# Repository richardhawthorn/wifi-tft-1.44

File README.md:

### Features

- ESP8266 wifi processor
- 128*128 SPI TFT screen
- FTDI chip + FTDI programming port
- 3.3V operation
- Mini USB power connector

### License

This work is licensed under a Creative Commons Attribution-ShareAlike 4.0 International License.

<br />
Designed by <a xmlns:cc="http://creativecommons.org/ns#" href="http://www.richardhawthorn.com" property="cc:attributionName" rel="cc:attributionURL" target="_blank">Richard Hawthorn</a><br />
<a rel="license" href="http://creativecommons.org/licenses/by-sa/4.0/" target="_blank">View License</a>

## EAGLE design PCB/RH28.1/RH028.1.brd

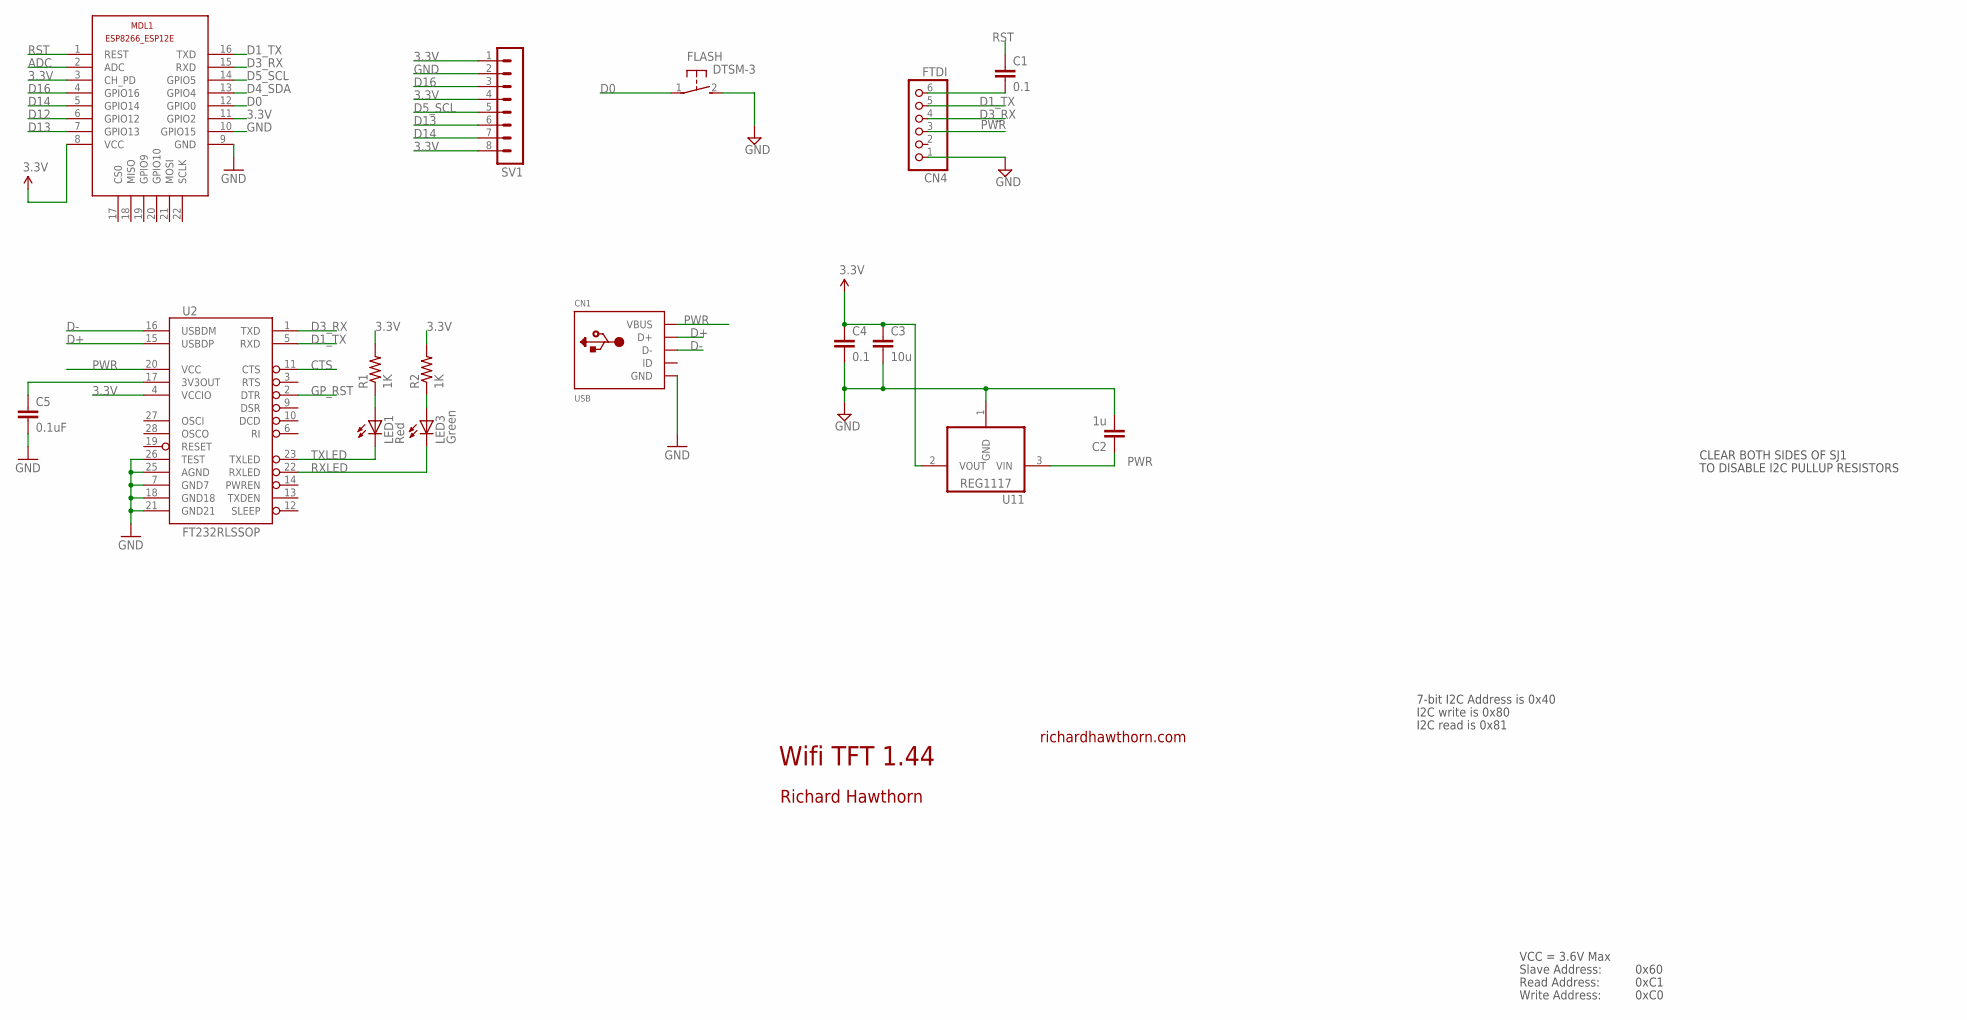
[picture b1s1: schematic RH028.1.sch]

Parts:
C1, C4: 0.1; 0603-CAP
C2: 1u; 0603-CAP
C3: 10u; 0805-CAP
C5: 0.1uF; 0402-CAP
CN1: USB; USB-MINIB
CN4: FTDI; 1X06
FLASH: DTSM-3
LED1: Red; LED-0603
LED3: Green; LED-0603
MDL1: ESP8266-12EESP8266-ESP12E; ESP8266-ESP12E
R1, R2: 1K; 0402-RES
SV1: MA08-1
U2: FT232RLSSOP; SSOP28DB
U11: REG1117; SOT223

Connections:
3.3V: C3.1, C4.1, MDL1.3 (CH_PD), MDL1.8 (VCC), MDL1.11 (GPIO2), R1.2, R2.2, SV1.1, SV1.4, SV1.8, U2.4 (VCCIO), U11.2 (VOUT)
3.3VOUT: C5.1, U2.17 (3V3OUT)
ADC: MDL1.2 (ADC)
CTS: U2.11 (CTS)
D0: FLASH.1, MDL1.12 (GPIO0)
D1_TX: CN4.5, MDL1.16 (TXD), U2.5 (RXD)
D3_RX: CN4.4, MDL1.15 (RXD), U2.1 (TXD)
D4_SDA: MDL1.13 (GPIO4)
D5_SCL: MDL1.14 (GPIO5), SV1.5
D12: MDL1.6 (GPIO12)
D13: MDL1.7 (GPIO13), SV1.6
D14: MDL1.5 (GPIO14), SV1.7
D16: MDL1.4 (GPIO16), SV1.3
D+: CN1.D+, U2.15 (USBDP)
D-: CN1.D-, U2.16 (USBDM)
GND: C2.2, C3.2, C4.2, C5.2, CN1.GND, CN4.1, FLASH.2, MDL1.9 (GND), MDL1.10 (GPIO15), SV1.2, U2.7 (GND7), U2.18 (GND18), U2.21 (GND21), U2.25 (AGND), U2.26 (TEST), U11.1 (GND)
GP_RST: U2.2 (DTR)
unnamed: LED1.A, R1.1
unnamed: LED3.A, R2.1
unnamed: C1.2, CN4.6
PWR: C2.1, CN1.VBUS, CN4.3, U2.20 (VCC), U11.3 (VIN)
RST: C1.1, MDL1.1 (REST)
RXLED: LED3.C, U2.22 (RXLED)
TXLED: LED1.C, U2.23 (TXLED)

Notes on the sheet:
Wifi TFT 1.44
richardhawthorn.com
Richard Hawthorn
CLEAR BOTH SIDES OF SJ1
TO DISABLE I2C PULLUP RESISTORS
7-bit I2C Address is 0x40
I2C write is 0x80
I2C read is 0x81
VCC = 3.6V Max
Read Address:
Write Address:
Slave Address:
0x60
0xC1
0xC0

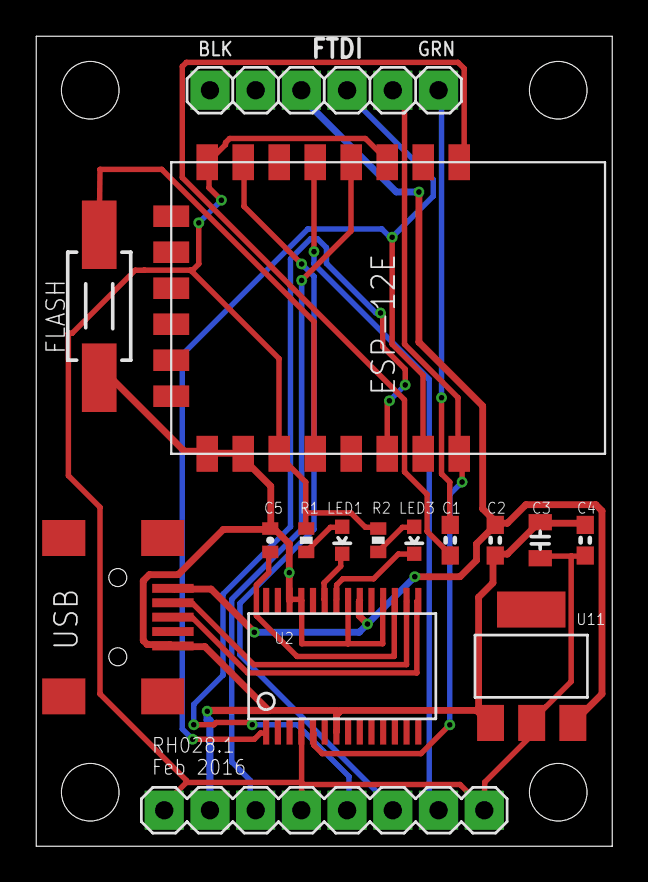
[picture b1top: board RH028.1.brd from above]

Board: 2 copper layers, 32.0 x 45.0 mm, 17 parts (1 on the bottom side), 19 nets.

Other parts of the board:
U$3: OSHW-LOGO-S

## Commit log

2016-11-08 added pcb files
2017-01-24 added demo code and images
2017-01-24 add image

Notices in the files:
parts and their libraries:
SparkFun-Aesthetics: Licensing: CC v3.0 Share-Alike You are welcome to use this library for commercial purposes.
